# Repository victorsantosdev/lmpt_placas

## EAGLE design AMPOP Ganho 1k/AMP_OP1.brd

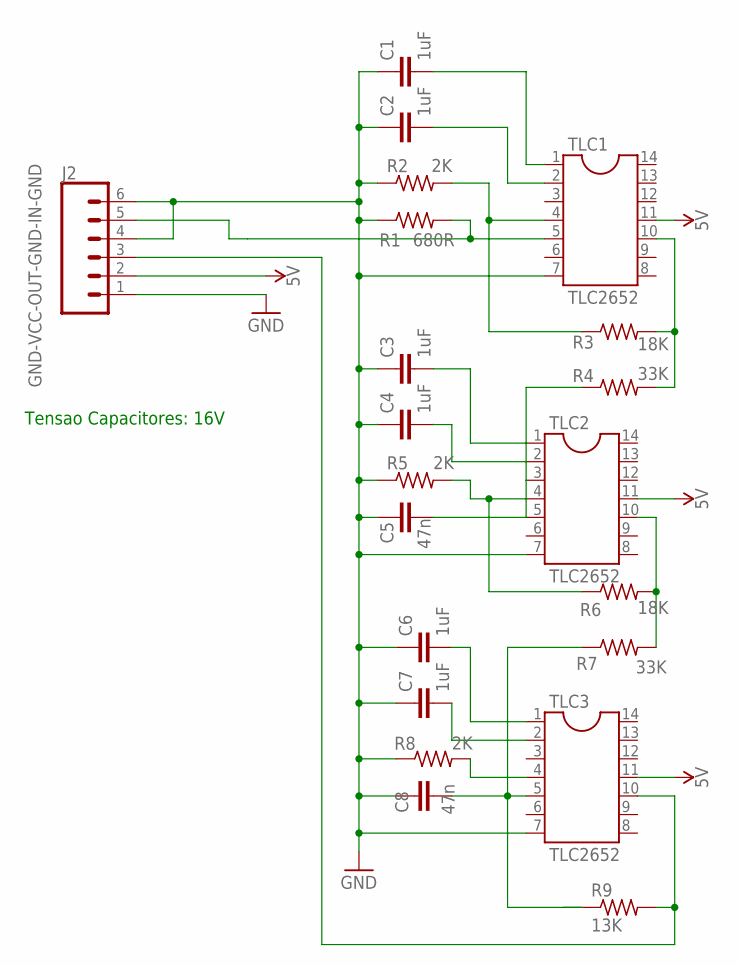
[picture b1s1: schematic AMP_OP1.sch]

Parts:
C1, C2, C3, C4, C6, C7: 1uF; C5B3.5
C5, C8: 47n; C5B3.5
J2: GND-VCC-OUT-GND-IN-GND; 1X06_LONGPADS
R1: 680R; 0207/9
R2, R5, R8: 2K; 0207/9
R3, R6: 18K; 0207/9
R4, R7: 33K; 0207/9
R9: 13K; 0207/9
TLC1, TLC2, TLC3: TLC2652; DIL14

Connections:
5V: J2.2, TLC1.11, TLC2.11, TLC3.11
GND: C1.1, C2.1, C3.1, C4.1, C5.1, C6.1, C7.1, C8.1, J2.1, J2.4, J2.6, R1.1, R2.1, R5.1, R8.1, TLC1.7, TLC2.7, TLC3.7
unnamed: C1.2, TLC1.1
unnamed: C2.2, TLC1.2
unnamed: C3.2, TLC2.1
unnamed: C4.2, TLC2.2
unnamed: C7.2, TLC3.2
unnamed: R2.2, R3.1, TLC1.4
unnamed: C6.2, TLC3.1
unnamed: J2.5, R1.2, TLC1.5
unnamed: R3.2, R4.2, TLC1.10
unnamed: C5.2, R4.1, TLC2.3, TLC2.5
unnamed: R5.2, R6.1, TLC2.4
unnamed: R8.2, TLC3.4
unnamed: C8.2, R7.1, R9.1, TLC3.5
unnamed: R6.2, R7.2, TLC2.10
unnamed: J2.3, R9.2, TLC3.10

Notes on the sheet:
Tensao Capacitores: 16V

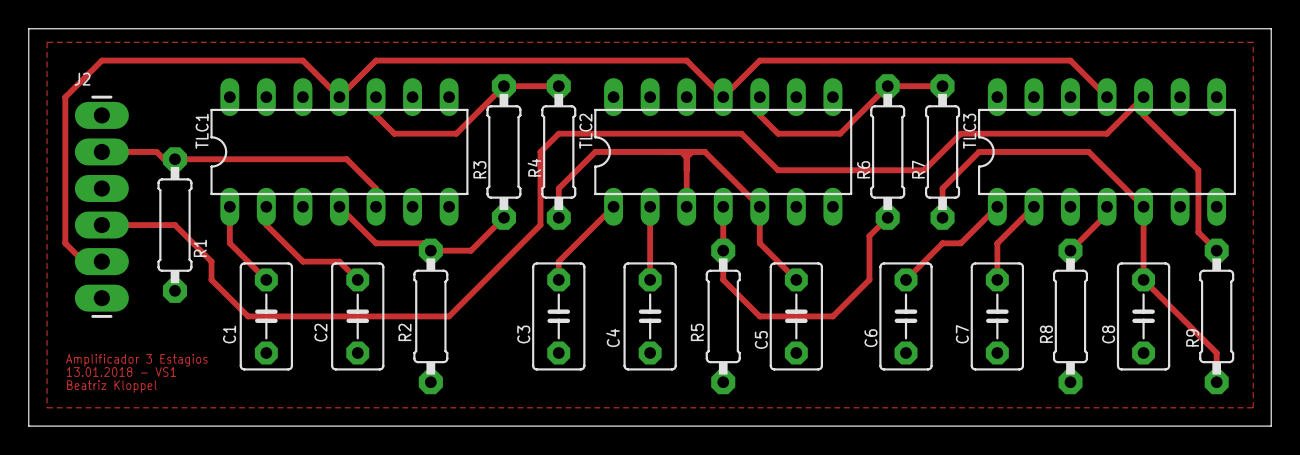
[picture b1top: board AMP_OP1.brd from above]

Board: 2 copper layers, 86.3 x 27.6 mm, 21 parts (0 on the bottom side), 17 nets.

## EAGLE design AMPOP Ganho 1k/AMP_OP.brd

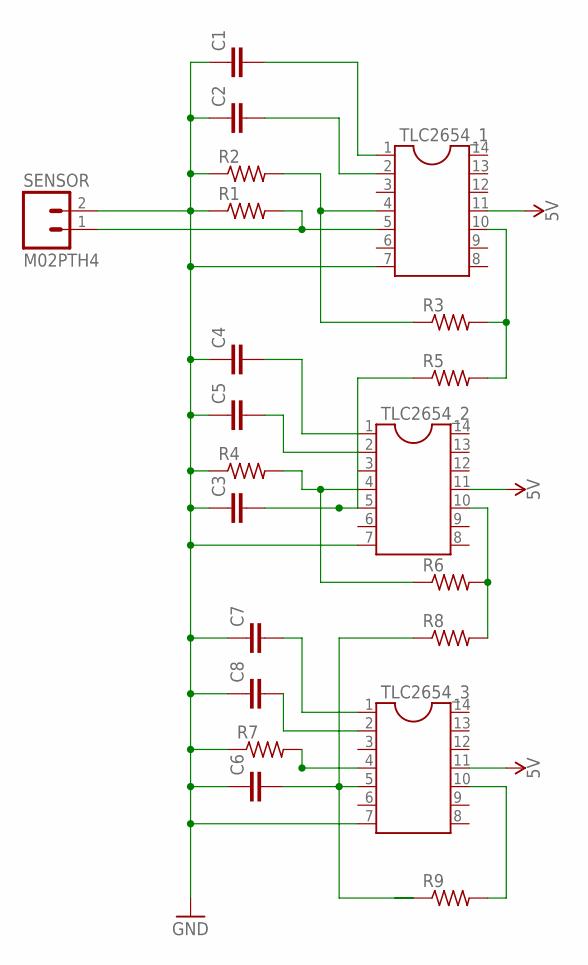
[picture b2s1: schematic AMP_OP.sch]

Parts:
C1, C2, C3, C4, C5, C6, C7, C8: C5/3.5; C5B3.5
R1, R2, R3, R4, R5, R6, R7, R8, R9: R-US_0207/9; 0207/9
SENSOR: M02PTH4; 1X02_XTRA_BIG
TLC2654_1, TLC2654_2, TLC2654_3: DIL14

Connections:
5V: TLC2654_1.11, TLC2654_2.11, TLC2654_3.11
GND: C1.1, C2.1, C3.1, C4.1, C5.1, C6.1, C7.1, C8.1, R1.1, R2.1, R4.1, R7.1, SENSOR.2, TLC2654_1.7, TLC2654_2.7, TLC2654_3.7
unnamed: C1.2, TLC2654_1.1
unnamed: C2.2, TLC2654_1.2
unnamed: C4.2, TLC2654_2.1
unnamed: C5.2, TLC2654_2.2
unnamed: C8.2, TLC2654_3.2
unnamed: R2.2, R3.1, TLC2654_1.4
unnamed: C7.2, TLC2654_3.1
unnamed: R1.2, SENSOR.1, TLC2654_1.5
unnamed: R3.2, R5.2, TLC2654_1.10
unnamed: C3.2, R5.1, TLC2654_2.5
unnamed: R4.2, R6.1, TLC2654_2.4
unnamed: R7.2, TLC2654_3.4
unnamed: C6.2, R8.1, R9.1, TLC2654_3.5
unnamed: R6.2, R8.2, TLC2654_2.10
unnamed: R9.2, TLC2654_3.10

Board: 2 copper layers, 21 parts (0 on the bottom side), 17 nets, no tracks yet.

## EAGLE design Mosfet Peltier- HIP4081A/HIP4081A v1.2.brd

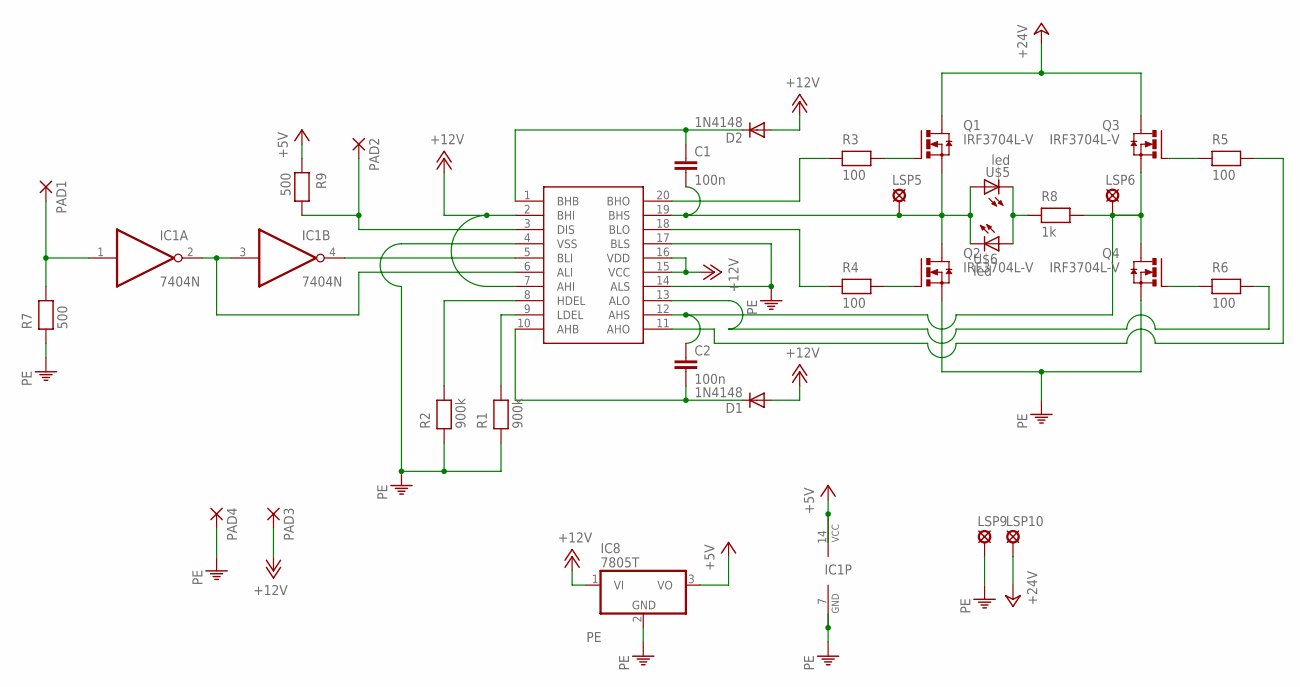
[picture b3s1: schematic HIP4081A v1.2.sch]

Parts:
C1, C2: 100n; C5B2.5
D1, D2: 1N4148; DO35-10
IC1: 7404N; DIL14
IC2: HIP4081A; DIL20
IC8: 7805T; TO220H
LSP5, LSP6, LSP9, LSP10: SE14
PAD1, PAD2, PAD3, PAD4: 1,6/0,8
Q1, Q2, Q3, Q4: IRF3704L-V; TO262-V
R1, R2: 900k; R-10
R3, R4, R5, R6: 100; R-10
R7, R9: 500; R-10
R8: 1k; R-10
U$5, U$6: led; LED3MM

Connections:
+5V: IC1.14 (VCC), IC8.3 (VO), R9.1
+12V: D1.A, D2.A, IC2.2 (BHI), IC2.7 (AHI), IC2.15 (VCC), IC2.16 (VDD), IC8.1 (VI), PAD3.1
+24V: LSP10.MP, Q1.2 (D), Q3.2 (D)
unnamed: C1.2, IC2.19 (BHS), LSP5.MP, Q1.3 (S), Q2.2 (D), U$5.A, U$6.K (C)
unnamed: C2.1, IC2.12 (AHS), LSP6.MP, Q3.3 (S), Q4.2 (D), R8.2
unnamed: IC2.20 (BHO), R3.1
unnamed: IC2.18 (BLO), R4.1
unnamed: IC1.4 (O), IC2.5 (BLI)
unnamed: R8.1, U$5.K (C), U$6.A
unnamed: IC2.9 (LDEL), R1.2
unnamed: IC2.8 (HDEL), R2.2
unnamed: C1.1, D2.C, IC2.1 (BHB)
unnamed: IC2.11 (AHO), R5.2
unnamed: IC2.13 (ALO), R6.2
unnamed: C2.2, D1.C, IC2.10 (AHB)
unnamed: IC2.3 (DIS), PAD2.1, R9.2
unnamed: Q2.1 (G), R4.2
unnamed: Q4.1 (G), R6.1
unnamed: Q3.1 (G), R5.1
unnamed: Q1.1 (G), R3.2
unnamed: IC1.1 (I), PAD1.1, R7.2
unnamed: IC1.2 (O), IC1.3 (I), IC2.6 (ALI)
PE: IC1.7 (GND), IC2.4 (VSS), IC2.14 (ALS), IC2.17 (BLS), IC8.2 (GND), LSP9.MP, PAD4.1, Q2.3 (S), Q4.3 (S), R1.1, R2.1, R7.1

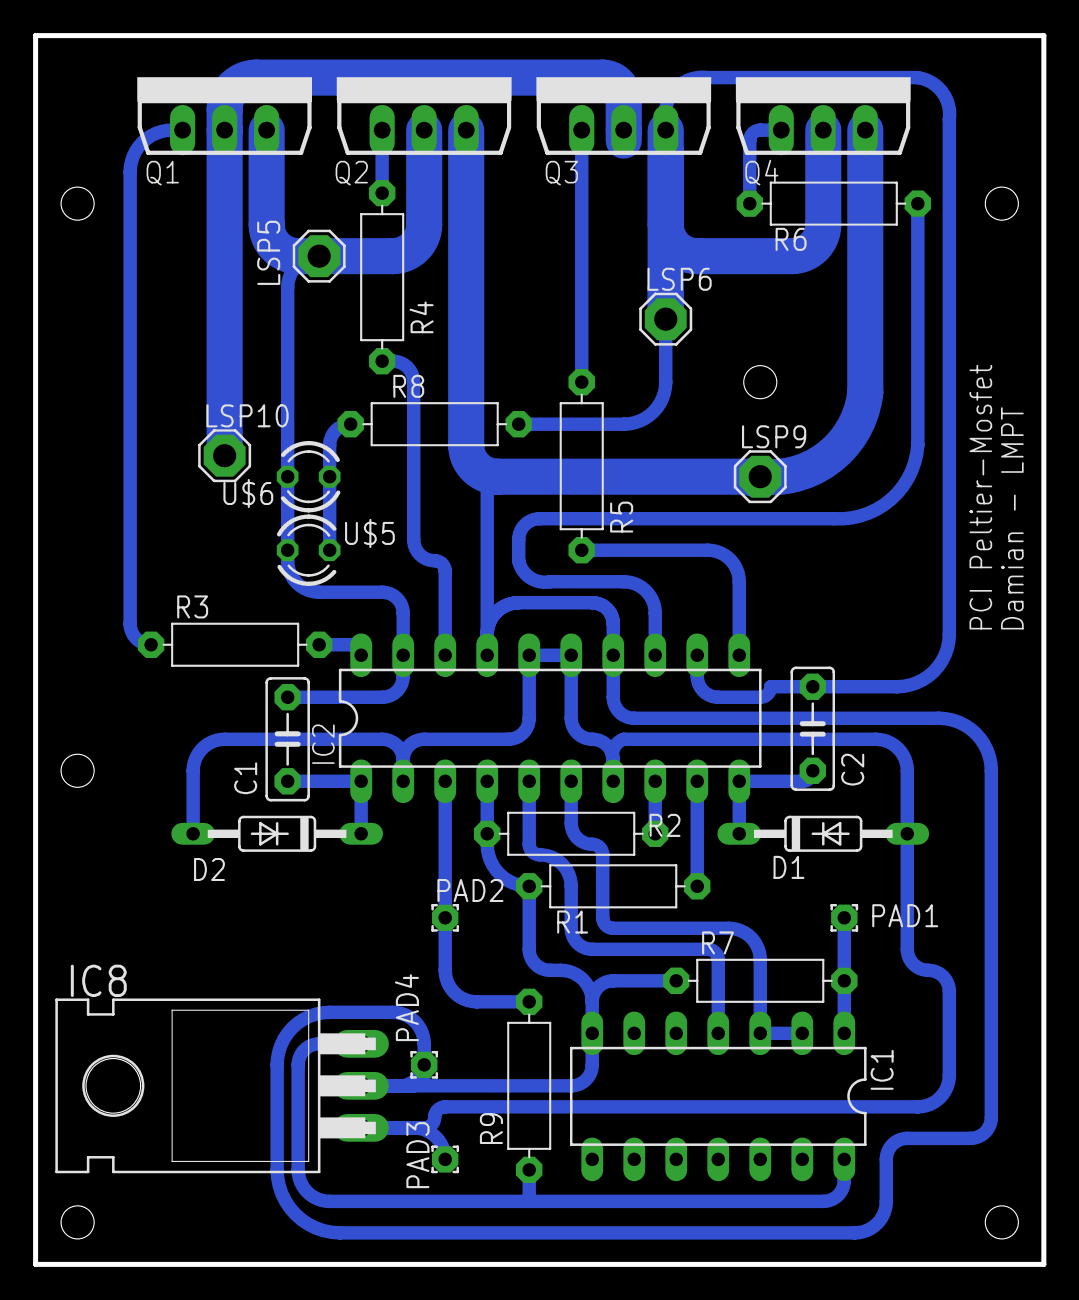
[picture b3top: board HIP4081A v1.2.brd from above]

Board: 1 copper layer, 61.0 x 74.3 mm, 30 parts (0 on the bottom side), 23 nets.

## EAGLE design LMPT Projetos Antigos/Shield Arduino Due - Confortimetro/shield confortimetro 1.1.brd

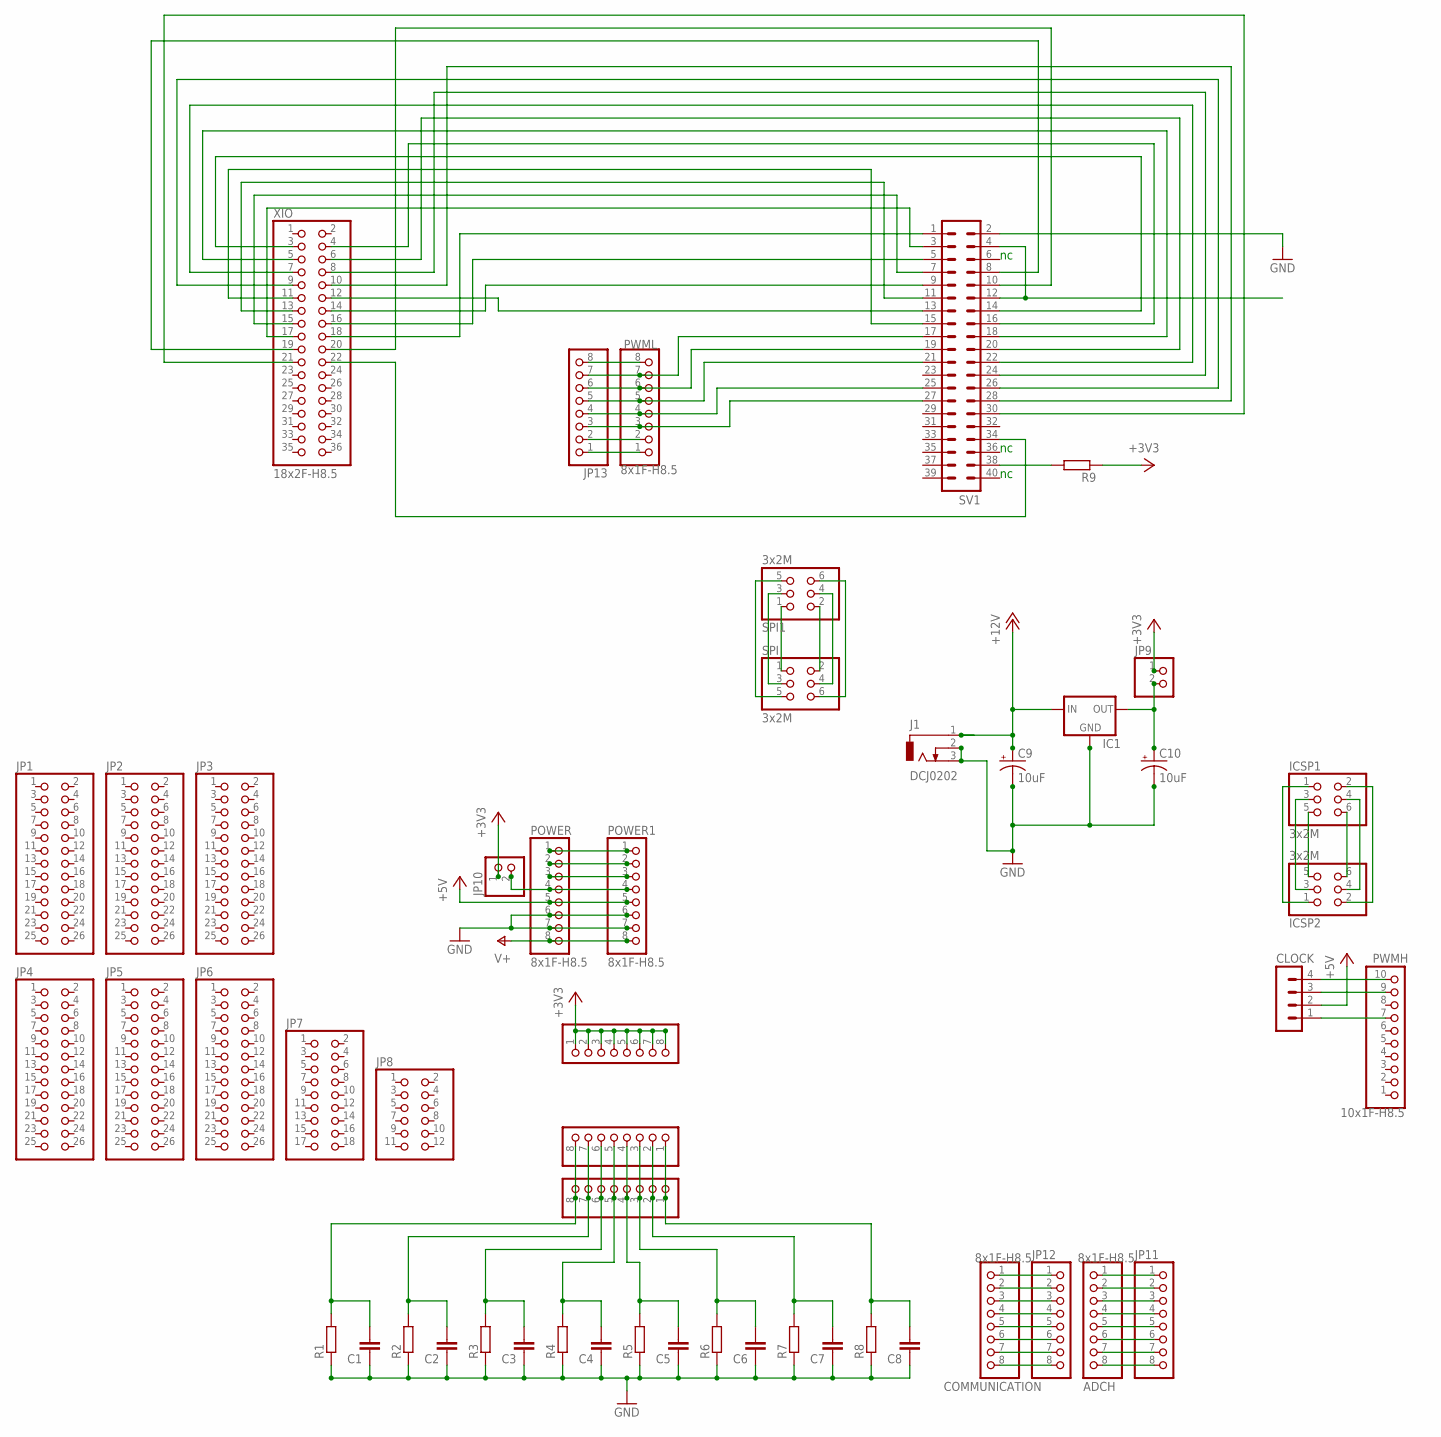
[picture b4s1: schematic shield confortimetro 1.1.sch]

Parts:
ADCH: 8x1F-H8.5; 1X08
ADCL: 8x1F-H8.5; 1X08
C1, C2, C3, C4, C5, C6, C7, C8: C5/2.5; C5B2.5
C9, C10: 10uF; E2-5
CLOCK: MA04-1
COMMUNICATION: 8x1F-H8.5; 1X08
IC1: 78XXL
ICSP1, ICSP2: 3x2M; 2X03
J1: DCJ0202
JP1, JP2, JP3, JP4, JP5, JP6: PINHD-2X13; 2X13
JP7: PINHD-2X9; 2X09
JP8: PINHD-2X6; 2X06
JP9, JP10: PINHD-1X2; 1X02
JP11, JP12, JP13: PINHD-1X8; 1X08
POWER, POWER1: 8x1F-H8.5; 1X08
PWMH: 10x1F-H8.5; 1X10
PWML, PWML1, PWML2: 8x1F-H8.5; 1X08
R1, R2, R3, R4, R5, R6, R7, R8, R9: R-EU_0204/7; 0204/7
SPI, SPI1: 3x2M; 2X03
SV1: ML40
XIO: 18x2F-H8.5; 2X18

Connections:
+3V3: JP9.1, JP10.1, PWML2.1, PWML2.2, PWML2.3, PWML2.4, PWML2.5, PWML2.6, PWML2.7, PWML2.8, R9.1
+5V: CLOCK.2, POWER.5, POWER1.5
+12V: C9.+, IC1.IN, J1.1
GND: C1.1, C2.1, C3.1, C4.1, C5.1, C6.1, C7.1, C8.1, C9.-, C10.-, IC1.GND, J1.2, J1.3, POWER.6, POWER.7, POWER1.6, POWER1.7, R1.1, R2.1, R3.1, R4.1, R5.1, R6.1, R7.1, R8.1, SV1.2
unnamed: ADCL.2, C7.2, PWML1.2, R7.2
unnamed: ADCL.8, C1.2, PWML1.8, R1.2
unnamed: ADCL.7, C2.2, PWML1.7, R2.2
unnamed: ADCL.6, C3.2, PWML1.6, R3.2
unnamed: ADCL.5, C4.2, PWML1.5, R4.2
unnamed: ADCL.4, C5.2, PWML1.4, R5.2
unnamed: POWER.1, POWER1.1
unnamed: POWER.2, POWER1.2
unnamed: POWER.3, POWER1.3
unnamed: ADCL.3, C6.2, PWML1.3, R6.2
unnamed: ADCL.1, C8.2, PWML1.1, R8.2
unnamed: ICSP1.5, ICSP2.5
unnamed: ICSP1.6, ICSP2.6
unnamed: ICSP1.3, ICSP2.3
unnamed: ICSP1.1, ICSP2.1
unnamed: ICSP1.4, ICSP2.4
unnamed: ICSP1.2, ICSP2.2
unnamed: SPI.1, SPI1.1
unnamed: SPI.2, SPI1.2
unnamed: SPI.3, SPI1.3
unnamed: SPI.4, SPI1.4
unnamed: SPI.6, SPI1.6
unnamed: SPI.5, SPI1.5
unnamed: SV1.1, XIO.18
unnamed: CLOCK.4, PWMH.10
unnamed: CLOCK.3, PWMH.9
unnamed: CLOCK.1, PWMH.7
unnamed: ADCH.1, JP11.1
unnamed: ADCH.8, JP11.8
unnamed: ADCH.7, JP11.7
unnamed: ADCH.6, JP11.6
unnamed: ADCH.5, JP11.5
unnamed: ADCH.4, JP11.4
unnamed: ADCH.3, JP11.3
unnamed: ADCH.2, JP11.2
unnamed: COMMUNICATION.8, JP12.8
unnamed: COMMUNICATION.7, JP12.7
unnamed: COMMUNICATION.6, JP12.6
unnamed: COMMUNICATION.5, JP12.5
unnamed: COMMUNICATION.4, JP12.4
unnamed: COMMUNICATION.3, JP12.3
unnamed: COMMUNICATION.2, JP12.2
unnamed: COMMUNICATION.1, JP12.1
unnamed: JP13.8, PWML.8
unnamed: JP13.7, PWML.7, SV1.17
unnamed: JP13.6, PWML.6, SV1.19
unnamed: JP13.5, PWML.5, SV1.21
unnamed: JP13.4, PWML.4, SV1.25
unnamed: JP13.3, PWML.3, SV1.27
unnamed: JP13.2, PWML.2
unnamed: JP13.1, PWML.1
unnamed: SV1.3, XIO.17
unnamed: SV1.5, XIO.16
unnamed: SV1.7, XIO.15
unnamed: SV1.9, XIO.14
unnamed: SV1.11, XIO.13
unnamed: SV1.13, XIO.12
unnamed: SV1.15, XIO.11
unnamed: SV1.14, XIO.3
unnamed: SV1.16, XIO.4
unnamed: SV1.18, XIO.5
unnamed: SV1.20, XIO.6
unnamed: SV1.22, XIO.7
unnamed: SV1.24, XIO.8
unnamed: SV1.26, XIO.9
unnamed: SV1.28, XIO.10
unnamed: SV1.30, XIO.21
unnamed: SV1.4, SV1.12
unnamed: SV1.10, XIO.20
unnamed: SV1.8, XIO.19
unnamed: SV1.34, XIO.22
unnamed: R9.2, SV1.38
unnamed: C10.+, IC1.OUT, JP9.2
unnamed: JP10.2, POWER.4, POWER1.4
V+: POWER.8, POWER1.8

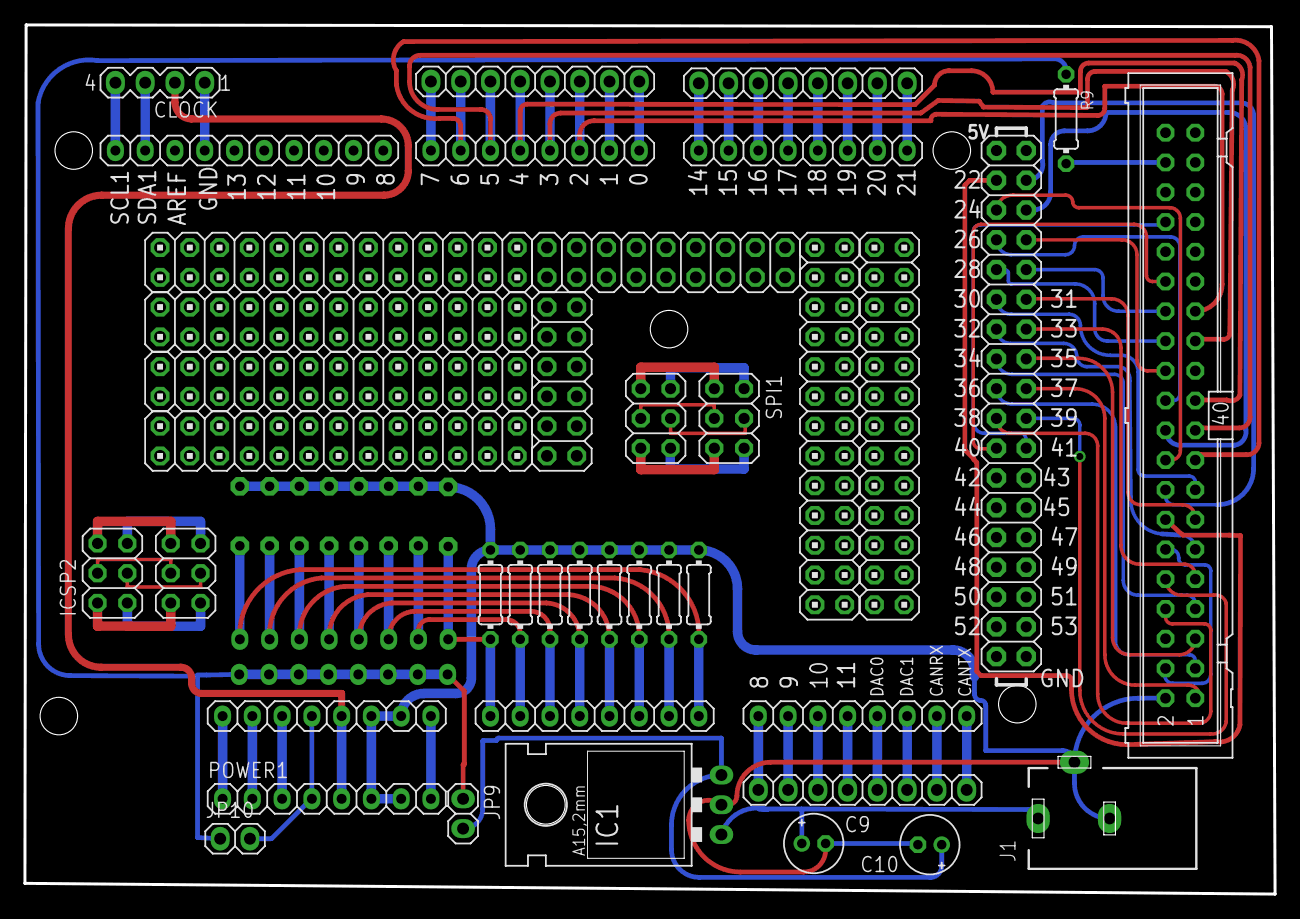
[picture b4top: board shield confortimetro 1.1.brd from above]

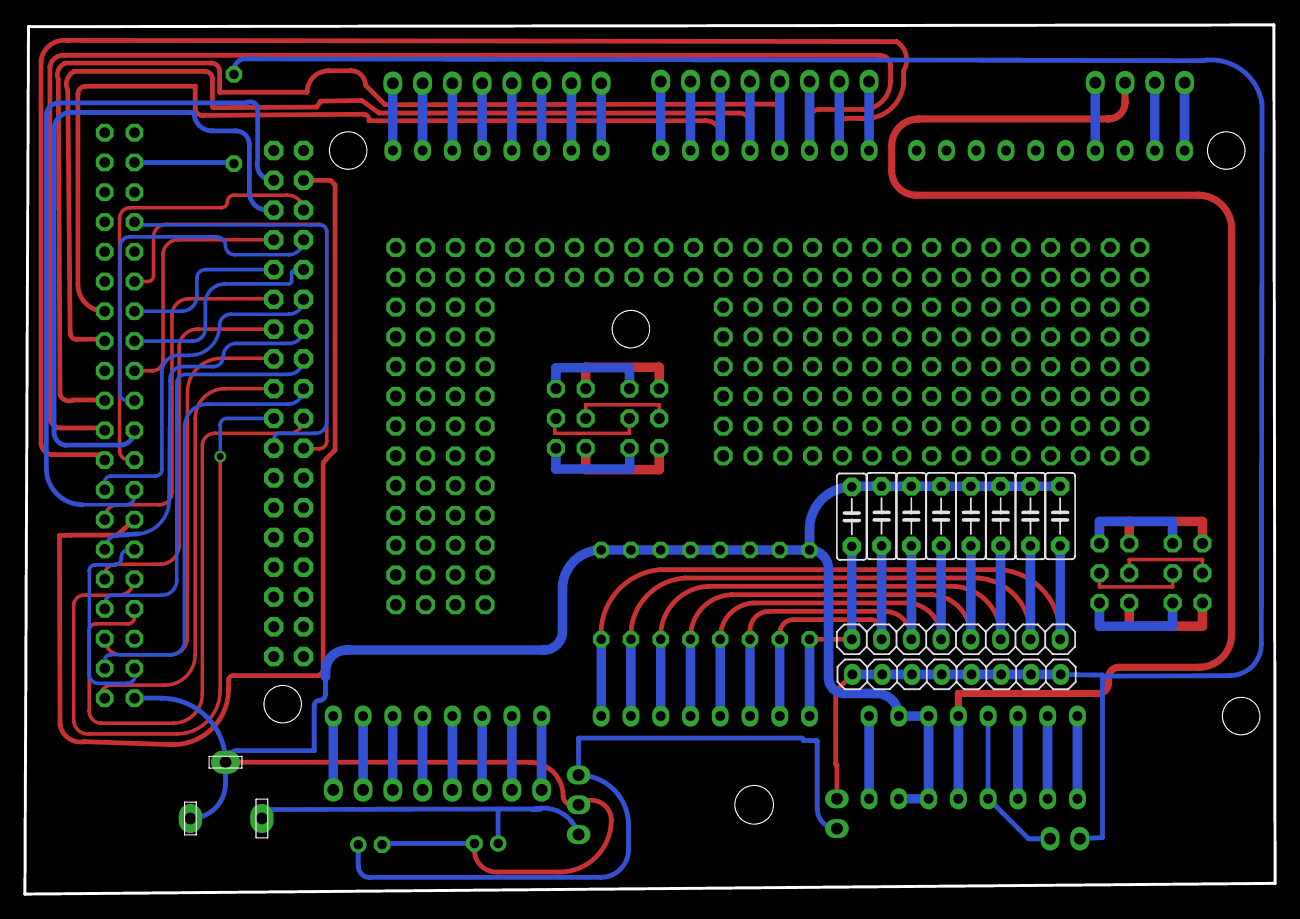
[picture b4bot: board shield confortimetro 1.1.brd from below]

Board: 2 copper layers, 106.7 x 74.2 mm, 50 parts (10 on the bottom side), 79 nets.

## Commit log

2017-03-19 Commit do remake das placas do ADS1248, rádio Xbee PRO 900HP S3B e Placa do regulador ADP3336ARMZ
2017-08-25 Adicionando as placas feitas na China (PCB Way): Leds, Conexoes_AD e Confortimetro.
2017-08-25 Diretorio do projeto confortimetro alterado.
2017-11-23 Adicionando as placas antigas do laboratorio.
2018-03-26 Adicionando as placas ampop ganho 1000 e Mosfet Peltier

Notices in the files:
parts and their libraries:
SparkFun-PowerSymbols: Licensing: Creative Commons ShareAlike 4.0 International - https://creativecommons.org/licenses/by-sa/4.0
